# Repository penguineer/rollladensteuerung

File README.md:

Rolladensteuerung
=================

Content

controller:       Relais-Controller Rollläden
manuellsteuerung: Schalter für Manuellbetrieb Rollläden
raspberry:        Software für den Kontroll-Raspy
relaiskarte:      Relais Rollläden
switchboard:      Altes Schalterboard
tuer-controller:  I2C-Bridge zur Tür-Steuerung
tuer-steuerung:   Kontrolle Motor und Türstatus-Schalter
wd-switch:        Watchdog-Switch für Reset per Raspy

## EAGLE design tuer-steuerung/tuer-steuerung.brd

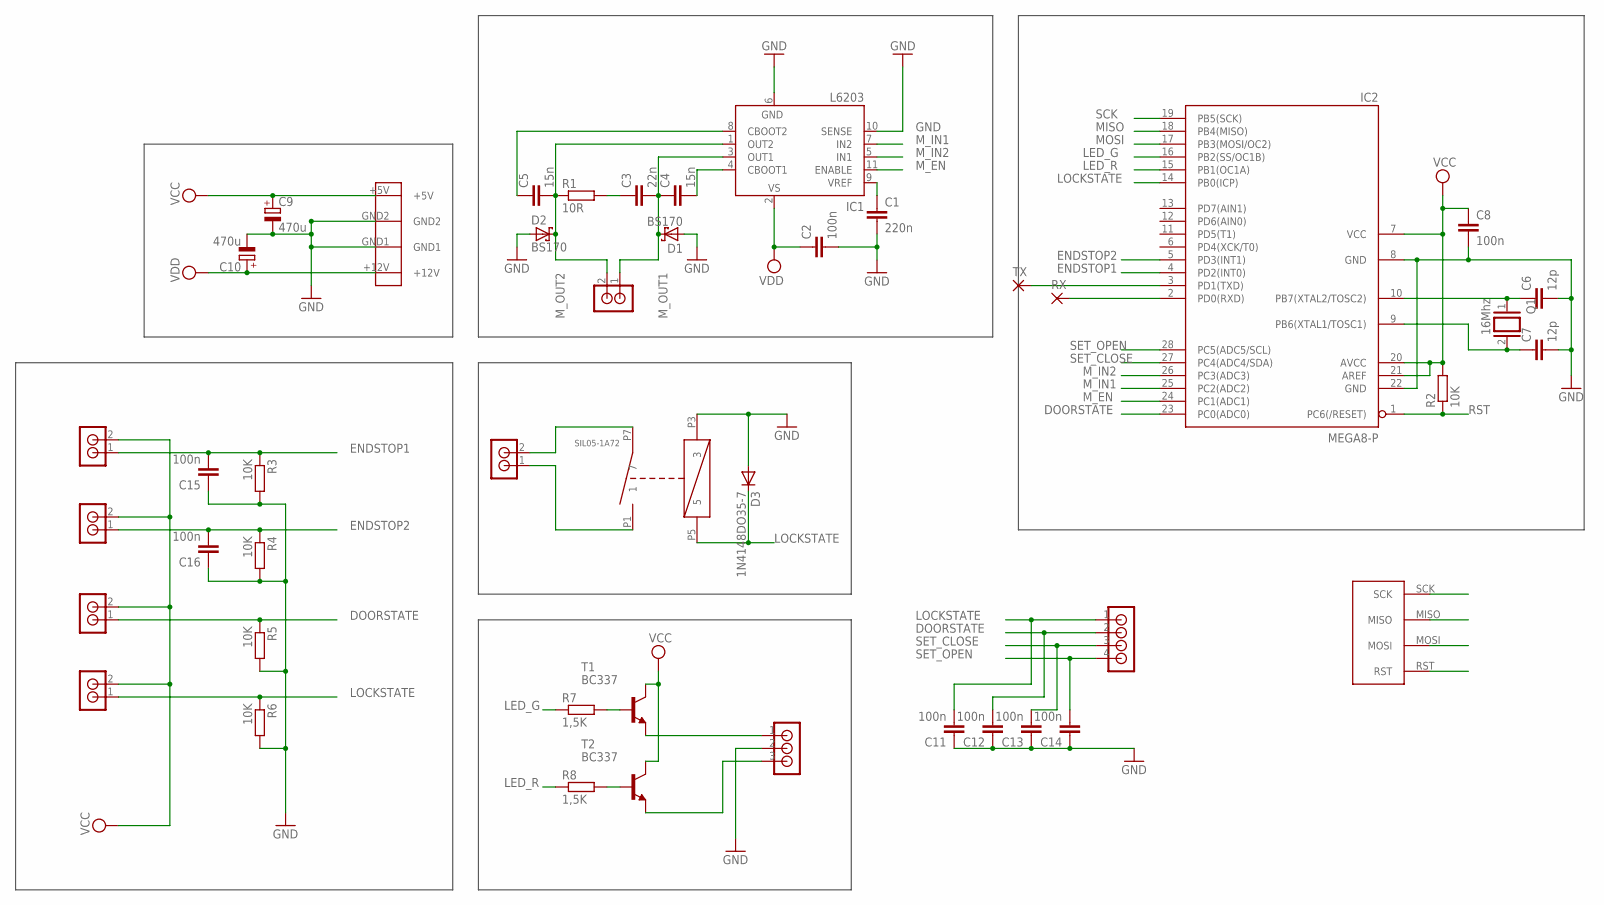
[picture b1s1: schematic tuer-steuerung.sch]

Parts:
C1: 220n; C025-024X044
C2, C8, C11, C12, C13, C14, C15, C16: 100n; C025-024X044
C3: 22n; C025-024X044
C4: 15n; C025-024X044
C5: 15n; C050-024X044
C6, C7: 12p; C050-025X075
C9, C10: 470u; TAP5-80
D1, D2: BS170; DO35-7
D3: 1N4148DO35-7; DO35-7
DOORSTATE: RIACON_101_2
ENDSTOP1, ENDSTOP2: RIACON_101_2
IC1: L6203; MULTIWATT-11
IC2: MEGA8-P; DIL28-3
LOCKSTATE: RIACON_101_2
MOTOR: RIACON_101_2
NERDSTERN: RIACON_101_2
Q1: 16Mhz; QS
R1: 10R; 0207/5V
R2, R3, R4, R5, R6: 10K; 0204/5
R7, R8: 1,5K; 0204/5
RX: 1,6/0,9
T1, T2: BC337; TO92
TX: 1,6/0,9
U$1: PSW_5
U$2: SIL05-1A72
U$3: AVR_ISP
U$4: RIACON_101_3
U$5: RIACON_101_4

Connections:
DOORSTATE: C12.2, DOORSTATE.1, IC2.23 (PC0(ADC0)), R5.1, U$5.2
ENDSTOP1: C15.2, ENDSTOP1.1, IC2.4 (PD2(INT0)), R3.1
ENDSTOP2: C16.2, ENDSTOP2.1, IC2.5 (PD3(INT1)), R4.1
GND: C1.2, C2.2, C6.2, C7.2, C8.2, C9.-, C10.-, C11.1, C12.1, C13.1, C14.1, C15.1, C16.1, D1.A, D2.A, D3.A, IC1.6 (GND), IC1.10 (SENSE), IC2.8 (GND), IC2.22 (GND), R3.2, R4.2, R5.2, R6.2, U$1.GND1, U$1.GND2, U$2.P3 (3), U$3.GND, U$4.2
LED_G: IC2.16 (PB2(SS/OC1B)), R7.1
LED_R: IC2.15 (PB1(OC1A)), R8.1
LOCKSTATE: C11.2, D3.C, IC2.14 (PB0(ICP)), LOCKSTATE.1, R6.1, U$2.P5 (5), U$5.1
MISO: IC2.18 (PB4(MISO)), U$3.MISO
MOSI: IC2.17 (PB3(MOSI/OC2)), U$3.MOSI
M_EN: IC1.11 (ENABLE), IC2.24 (PC1(ADC1))
M_IN1: IC1.7 (IN2), IC2.25 (PC2(ADC2))
M_IN2: IC1.5 (IN1), IC2.26 (PC3(ADC3))
M_OUT1: C3.2, C4.1, D1.C, IC1.3 (OUT1), MOTOR.1
M_OUT2: C5.2, D2.C, IC1.1 (OUT2), MOTOR.2, R1.1
unnamed: C6.1, IC2.10 (PB7(XTAL2/TOSC2)), Q1.1
unnamed: C7.1, IC2.9 (PB6(XTAL1/TOSC1)), Q1.2
unnamed: C1.1, IC1.9 (VREF)
unnamed: NERDSTERN.2, U$2.P7 (7)
unnamed: NERDSTERN.1, U$2.P1 (1)
unnamed: C3.1, R1.2
unnamed: C4.2, IC1.4 (CBOOT1)
unnamed: C5.1, IC1.8 (CBOOT2)
unnamed: R7.2, T1.2 (B)
unnamed: R8.2, T2.2 (B)
unnamed: T1.1 (E), U$4.1
unnamed: T2.1 (E), U$4.3
unnamed: IC2.3 (PD1(TXD)), TX.1
unnamed: IC2.2 (PD0(RXD)), RX.1
RST: IC2.1 (PC6(/RESET)), R2.1, U$3.RST
SCK: IC2.19 (PB5(SCK)), U$3.SCK
SET_CLOSE: C13.2, IC2.27 (PC4(ADC4/SDA)), U$5.3
SET_OPEN: C14.2, IC2.28 (PC5(ADC5/SCL)), U$5.4
VCC: C8.1, C9.+, DOORSTATE.2, ENDSTOP1.2, ENDSTOP2.2, IC2.7 (VCC), IC2.20 (AVCC), IC2.21 (AREF), LOCKSTATE.2, R2.2, T1.3 (C), T2.3 (C), U$1.+5V, U$3.VCC
VDD: C2.1, C10.+, IC1.2 (VS), U$1.+12V

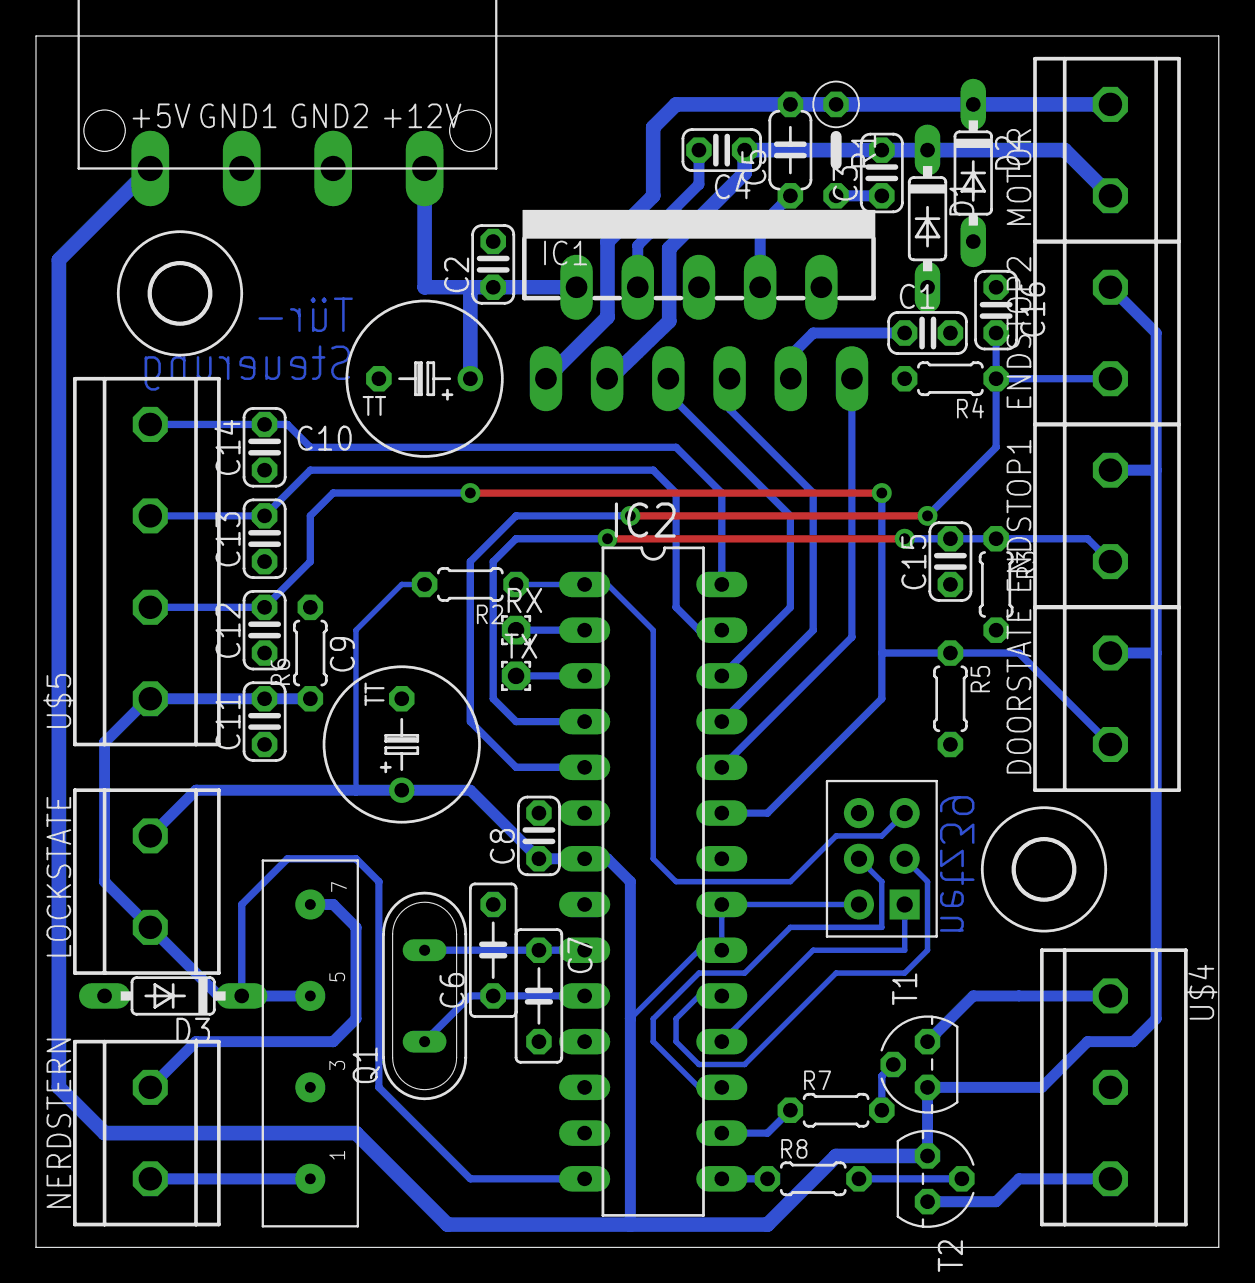
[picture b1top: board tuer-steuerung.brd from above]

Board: 2 copper layers, 65.7 x 67.3 mm, 47 parts (0 on the bottom side), 34 nets.

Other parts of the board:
U$6, U$7: 3,2

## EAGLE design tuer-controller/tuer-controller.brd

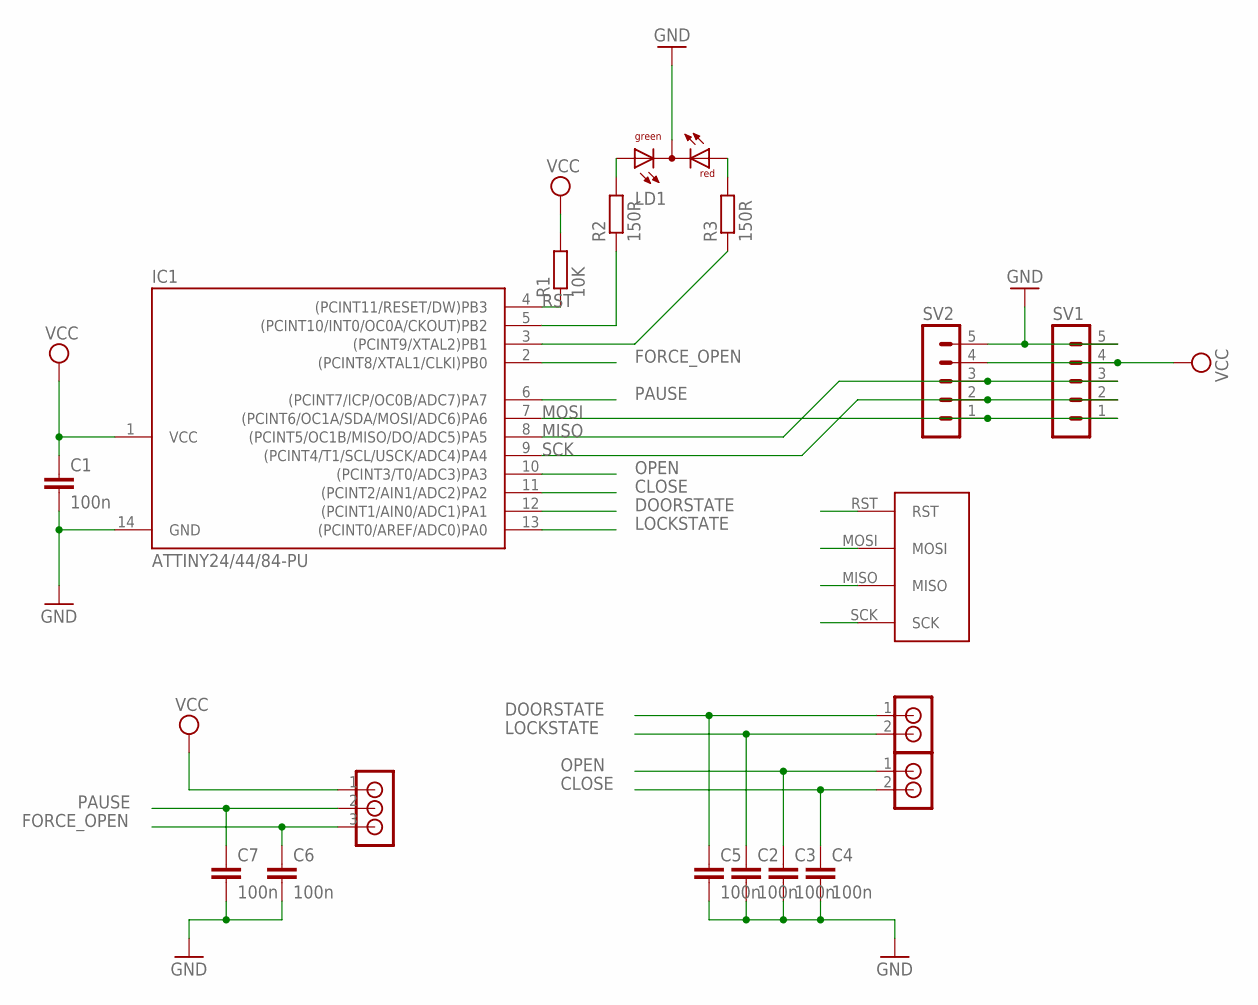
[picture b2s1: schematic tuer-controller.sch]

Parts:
C1, C2, C3, C4, C5, C6, C7: 100n; C025-024X044
IC1: ATTINY24/44/84-PU; DIL14
LD1: DUOLED-RG-C; DUOLED-C-5MM
R1: 10K; 0207/5V
R2: 150R; 0207/10
R3: 150R; 0207/15
SV1, SV2: MA05-1
U$1: AVR_ISP
U$2, U$3: RIACON_101_2
U$5: RIACON_59_3

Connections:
CLOSE: C4.1, IC1.11 ((PCINT2/AIN1/ADC2)PA2), U$3.2
DOORSTATE: C5.1, IC1.12 ((PCINT1/AIN0/ADC1)PA1), U$2.1
FORCE_OPEN: C6.1, IC1.2 ((PCINT8/XTAL1/CLKI)PB0), U$5.3
GND: C1.2, C2.2, C3.2, C4.2, C5.2, C6.2, C7.2, IC1.14 (GND), LD1.C, SV1.5, SV2.5, U$1.GND
LOCKSTATE: C2.1, IC1.13 ((PCINT0/AREF/ADC0)PA0), U$2.2
MISO: IC1.8 ((PCINT5/OC1B/MISO/DO/ADC5)PA5), SV1.3, SV2.3, U$1.MISO
MOSI: IC1.7 ((PCINT6/OC1A/SDA/MOSI/ADC6)PA6), SV1.1, SV2.1, U$1.MOSI
unnamed: IC1.5 ((PCINT10/INT0/OC0A/CKOUT)PB2), R2.1
unnamed: IC1.3 ((PCINT9/XTAL2)PB1), R3.1
unnamed: LD1.AX (AG), R2.2
unnamed: LD1.AR, R3.2
OPEN: C3.1, IC1.10 ((PCINT3/T0/ADC3)PA3), U$3.1
PAUSE: C7.1, IC1.6 ((PCINT7/ICP/OC0B/ADC7)PA7), U$5.2
RST: IC1.4 ((PCINT11/RESET/DW)PB3), R1.1, U$1.RST
SCK: IC1.9 ((PCINT4/T1/SCL/USCK/ADC4)PA4), SV1.2, SV2.2, U$1.SCK
VCC: C1.1, IC1.1 (VCC), R1.2, SV1.4, SV2.4, U$1.VCC, U$5.1

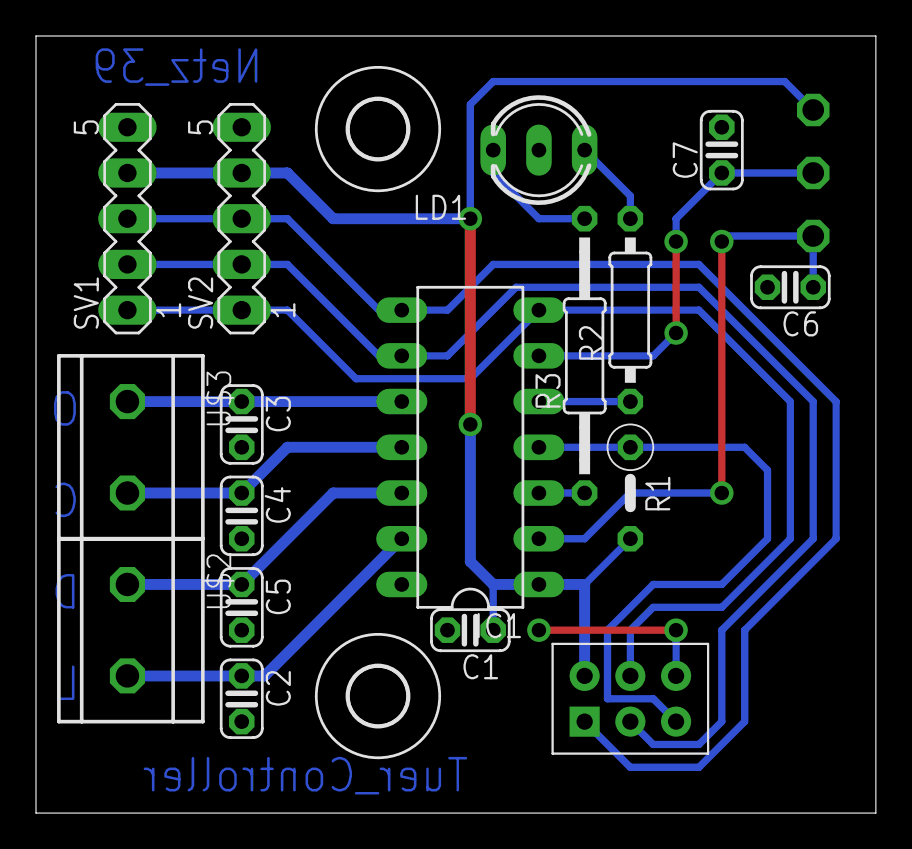
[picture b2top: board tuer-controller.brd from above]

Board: 2 copper layers, 46.7 x 43.2 mm, 20 parts (1 on the bottom side), 16 nets.

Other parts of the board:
U$4, U$6: 3,2

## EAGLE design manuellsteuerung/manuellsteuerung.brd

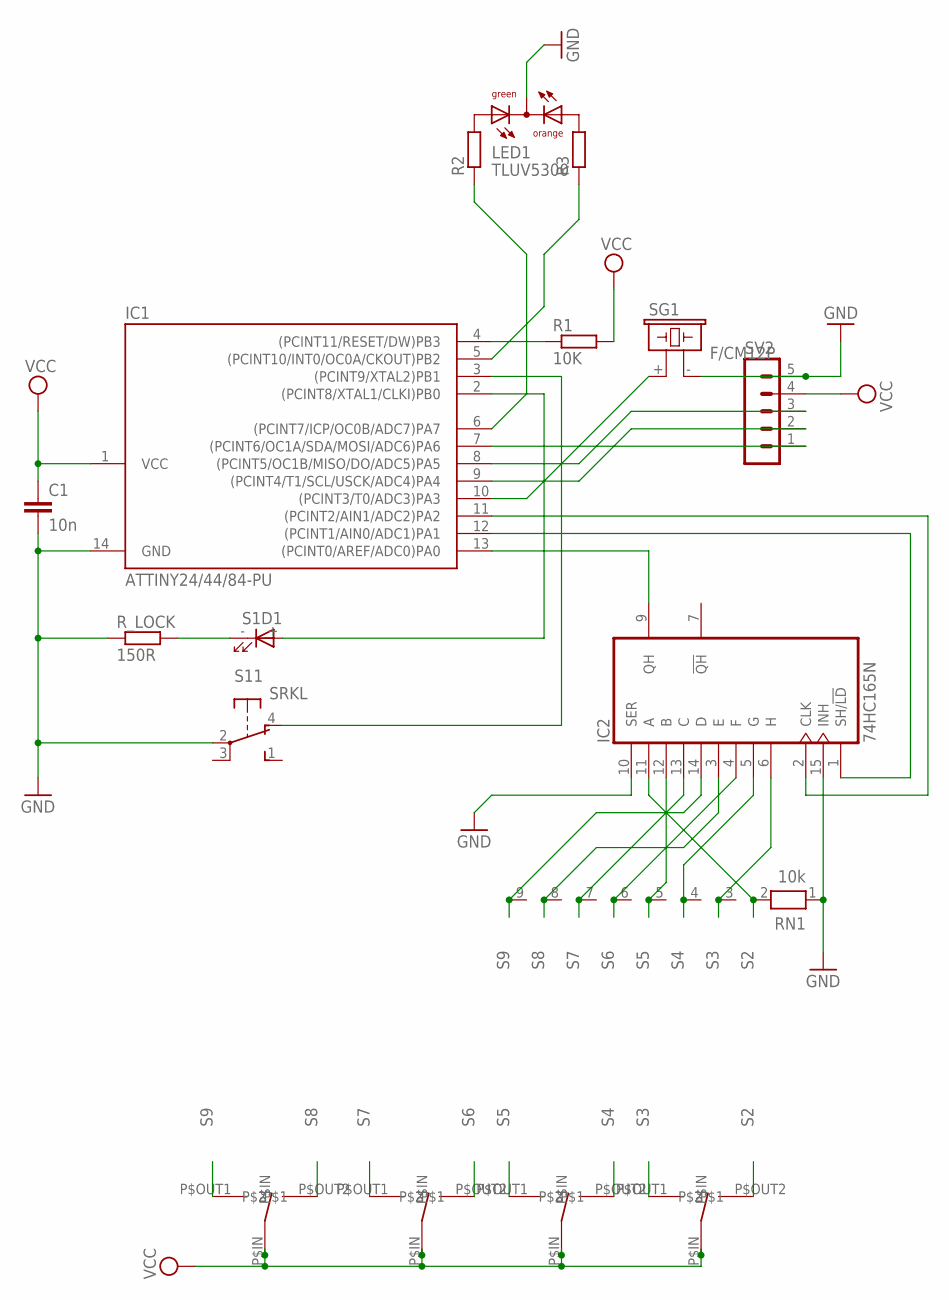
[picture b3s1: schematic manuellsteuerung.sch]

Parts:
C1: 10n; C025-024X044
IC1: ATTINY24/44/84-PU; DIL14
IC2: 74HC165N; DIL16
LED1: TLUV5300
R1: 10K; 0207/7
R2, R3: R-EU_0207/7; 0207/7
RN1: 10k; RN-9
R_LOCK: 150R; 0207/10
S1: SRKL
SG1: F/CM12P
SV2: MA05-1
U$1, U$2, U$3, U$4: MS_500E

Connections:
GND: C1.2, IC1.14 (GND), IC2.8 (GND), IC2.10 (SER), IC2.15 (INH), LED1.CC, RN1.1, R_LOCK.1, S1.2, SG1.- (2), SV2.5
MISO: IC1.8 ((PCINT5/OC1B/MISO/DO/ADC5)PA5), SV2.3
MOSI: IC1.7 ((PCINT6/OC1A/SDA/MOSI/ADC6)PA6), SV2.1
unnamed: IC1.13 ((PCINT0/AREF/ADC0)PA0), IC2.9 (QH)
unnamed: IC1.12 ((PCINT1/AIN0/ADC1)PA1), IC2.1 (SH/!LD)
unnamed: IC1.11 ((PCINT2/AIN1/ADC2)PA2), IC2.2 (CLK)
unnamed: R_LOCK.2, S1.- (C)
unnamed: IC1.2 ((PCINT8/XTAL1/CLKI)PB0), S1.+ (A)
unnamed: IC1.3 ((PCINT9/XTAL2)PB1), S1.4 (O)
unnamed: IC1.10 ((PCINT3/T0/ADC3)PA3), SG1.+ (1)
unnamed: LED1.AG, R2.2
unnamed: LED1.AO, R3.2
unnamed: IC1.6 ((PCINT7/ICP/OC0B/ADC7)PA7), R2.1
unnamed: IC1.5 ((PCINT10/INT0/OC0A/CKOUT)PB2), R3.1
RESET: IC1.4 ((PCINT11/RESET/DW)PB3), R1.1
S2: IC2.11 (A), RN1.2, U$4.P$OUT2
S3: IC2.6 (H), RN1.3, U$4.P$OUT1
S4: IC2.5 (G), RN1.4, U$1.P$OUT2
S5: IC2.12 (B), RN1.5, U$1.P$OUT1
S6: IC2.4 (F), RN1.6, U$3.P$OUT2
S7: IC2.13 (C), RN1.7, U$3.P$OUT1
S8: IC2.3 (E), RN1.8, U$2.P$OUT2
S9: IC2.14 (D), RN1.9, U$2.P$OUT1
SCK: IC1.9 ((PCINT4/T1/SCL/USCK/ADC4)PA4), SV2.2
VCC: C1.1, IC1.1 (VCC), IC2.16 (VCC), R1.2, SV2.4, U$1.P$IN, U$2.P$IN, U$3.P$IN, U$4.P$IN

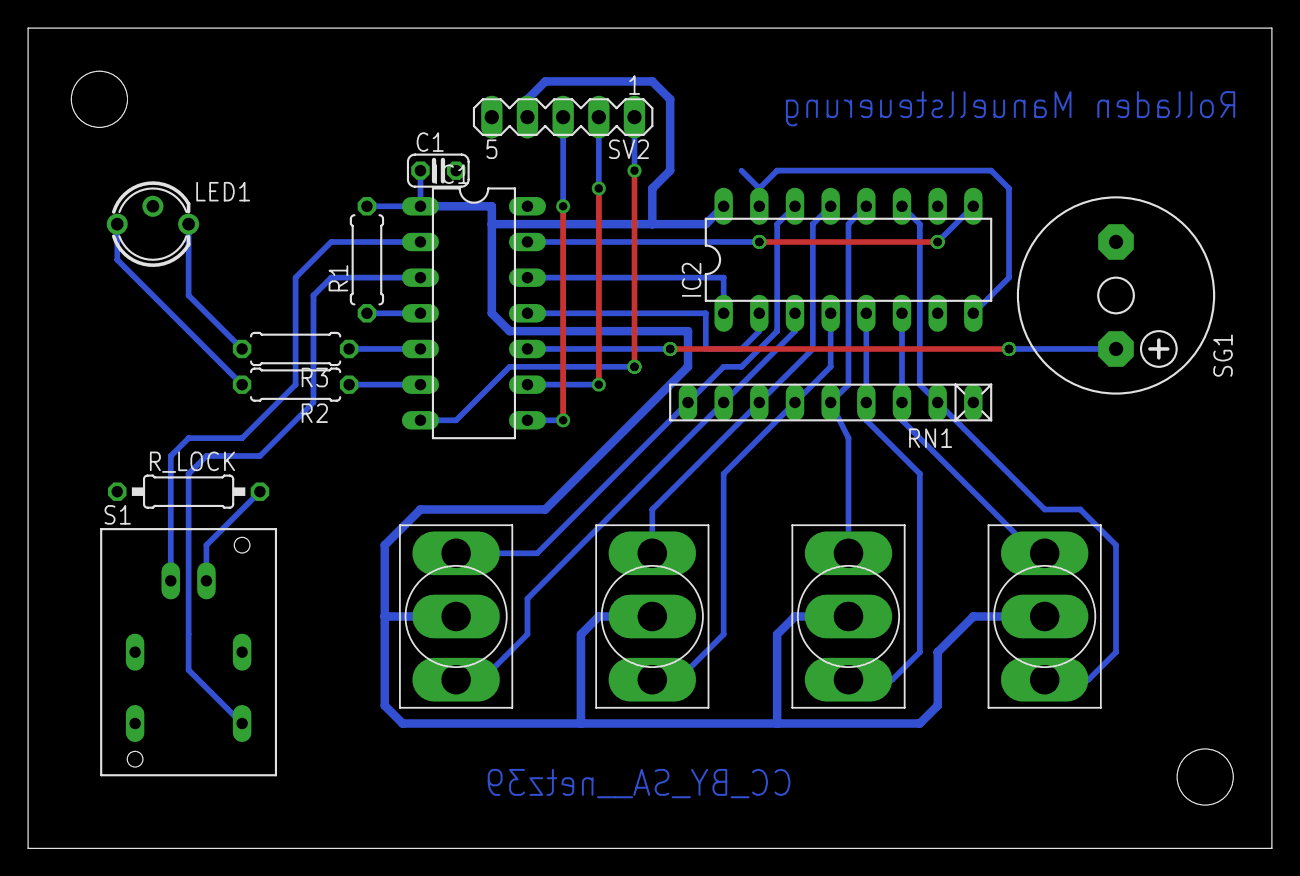
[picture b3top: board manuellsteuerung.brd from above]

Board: 2 copper layers, 88.6 x 58.4 mm, 16 parts (0 on the bottom side), 25 nets.

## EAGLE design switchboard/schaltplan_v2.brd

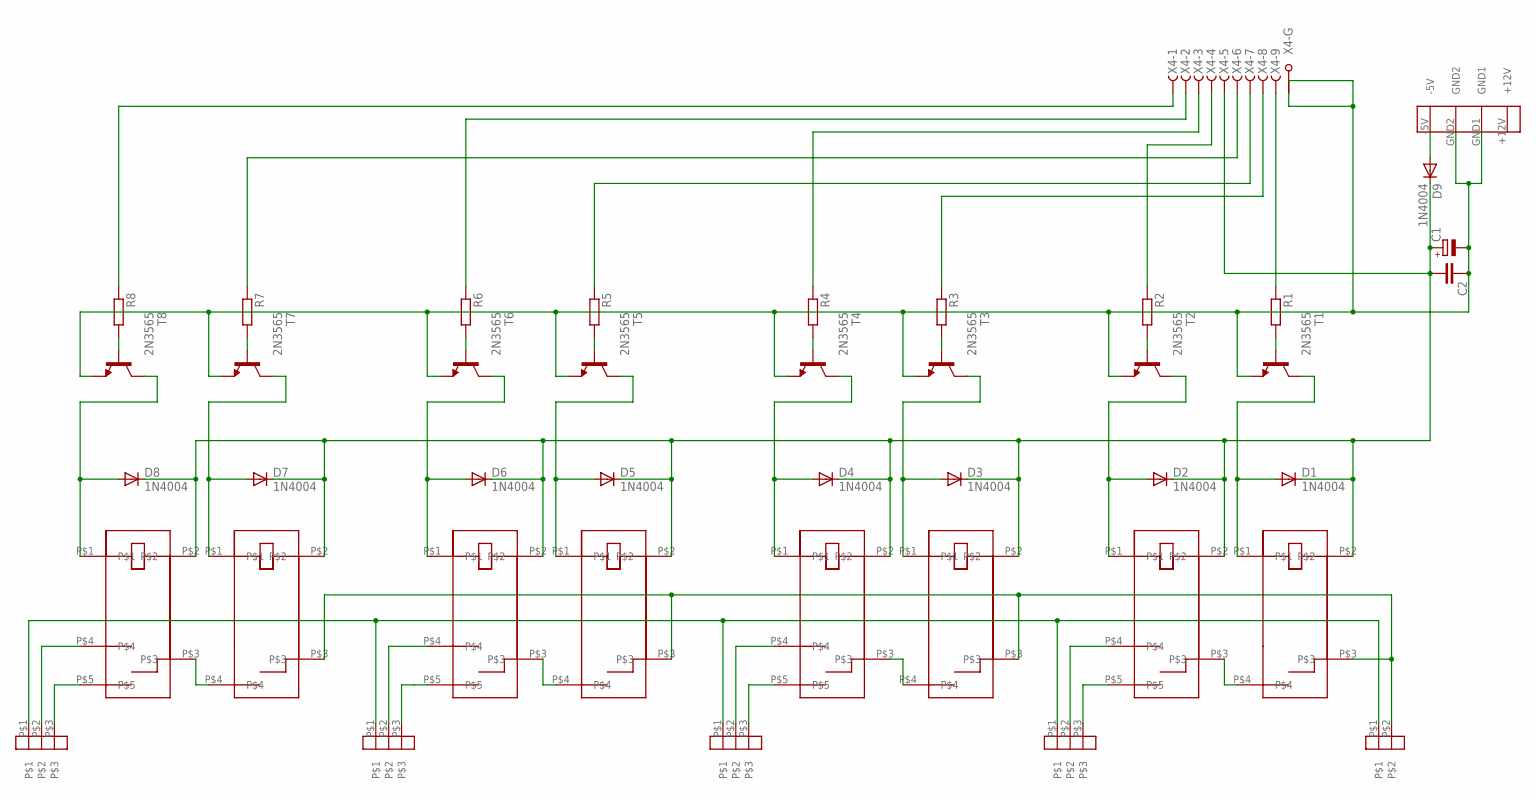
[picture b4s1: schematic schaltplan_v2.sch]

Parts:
C1: CPOL-EUE3.5-8; E3,5-8
C2: C-EU025-030X050; C025-030X050
D1, D2, D3, D4, D5, D6, D7, D8, D9: 1N4004; DO41-10
R1, R2, R3, R4, R5, R6, R7, R8: R-EU_0207/7; 0207/7
T1, T2, T3, T4, T5, T6, T7, T8: 2N3565; TO92
U$1, U$3, U$5, U$7: JS_05_MN_KT
U$2, U$4, U$6, U$8: JS_05_N_K
U$9: WAGO_734_262
U$10, U$11, U$12, U$13: WAGO_734_263
U$14: PSW_5
X4: F09HPS; F09HP

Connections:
GND: C1.-, C2.1, T1.3 (E), T2.3 (E), T3.3 (E), T4.3 (E), T5.3 (E), T6.3 (E), T7.3 (E), T8.3 (E), U$14.GND1, U$14.GND2, X4.G1, X4.G2
GND2: U$9.P$1, U$10.P$1, U$11.P$1, U$12.P$1, U$13.P$1
unnamed: U$2.P$5, U$10.P$3
unnamed: U$2.P$4, U$10.P$2
unnamed: U$1.P$4, U$2.P$3
unnamed: U$1.P$3, U$3.P$3, U$5.P$3, U$7.P$3, U$9.P$2
unnamed: D1.A, T1.1 (C), U$1.P$1
unnamed: D9.A, U$14.-5V
unnamed: R1.2, T1.2 (B)
unnamed: D2.A, T2.1 (C), U$2.P$1
unnamed: R5.1, X4.7 (F)
unnamed: D3.A, T3.1 (C), U$3.P$1
unnamed: R6.2, T6.2 (B)
unnamed: R6.1, X4.2 (F)
unnamed: R8.1, X4.1 (F)
unnamed: U$4.P$5, U$11.P$3
unnamed: U$4.P$4, U$11.P$2
unnamed: U$3.P$4, U$4.P$3
unnamed: D4.A, T4.1 (C), U$4.P$1
unnamed: R7.1, X4.6 (F)
unnamed: R3.2, T3.2 (B)
unnamed: R4.1, X4.3 (F)
unnamed: D5.A, T5.1 (C), U$5.P$1
unnamed: R2.1, X4.4 (F)
unnamed: R2.2, T2.2 (B)
unnamed: R4.2, T4.2 (B)
unnamed: U$6.P$5, U$12.P$3
unnamed: U$6.P$4, U$12.P$2
unnamed: U$5.P$4, U$6.P$3
unnamed: D6.A, T6.1 (C), U$6.P$1
unnamed: D7.A, T7.1 (C), U$7.P$1
unnamed: D8.A, T8.1 (C), U$8.P$1
unnamed: R5.2, T5.2 (B)
unnamed: R3.1, X4.8 (F)
unnamed: R1.1, X4.9 (F)
unnamed: R8.2, T8.2 (B)
unnamed: U$8.P$5, U$13.P$3
unnamed: U$8.P$4, U$13.P$2
unnamed: U$7.P$4, U$8.P$3
unnamed: R7.2, T7.2 (B)
V+: C1.+, C2.2, D1.C, D2.C, D3.C, D4.C, D5.C, D6.C, D7.C, D8.C, D9.C, U$1.P$2, U$2.P$2, U$3.P$2, U$4.P$2, U$5.P$2, U$6.P$2, U$7.P$2, U$8.P$2, X4.5 (F)

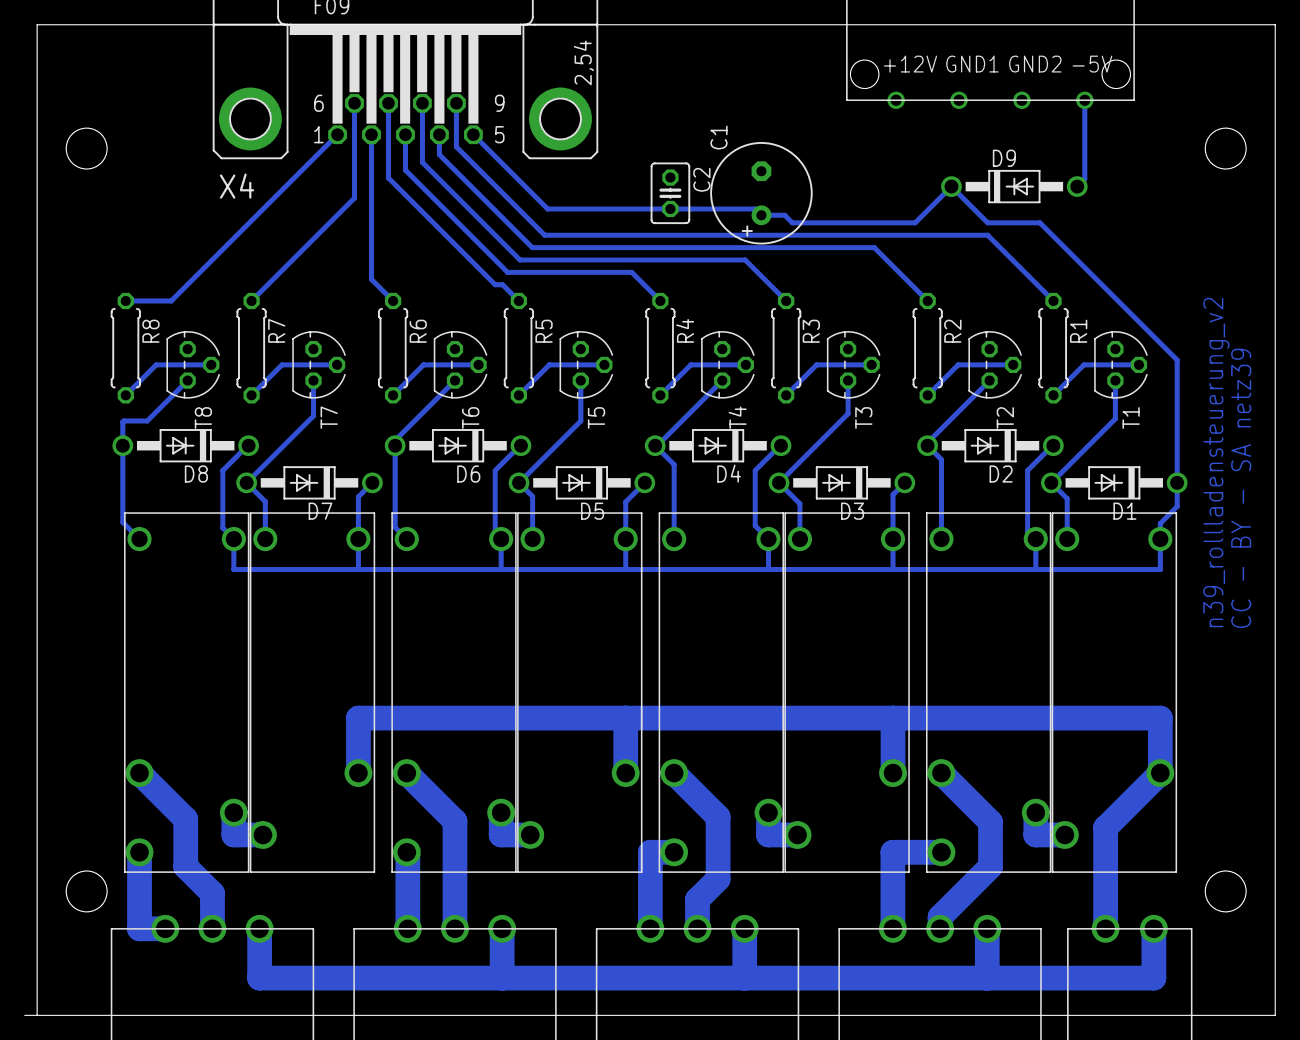
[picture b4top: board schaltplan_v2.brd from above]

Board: 2 copper layers, 101.0 x 80.0 mm, 42 parts (0 on the bottom side), 41 nets.

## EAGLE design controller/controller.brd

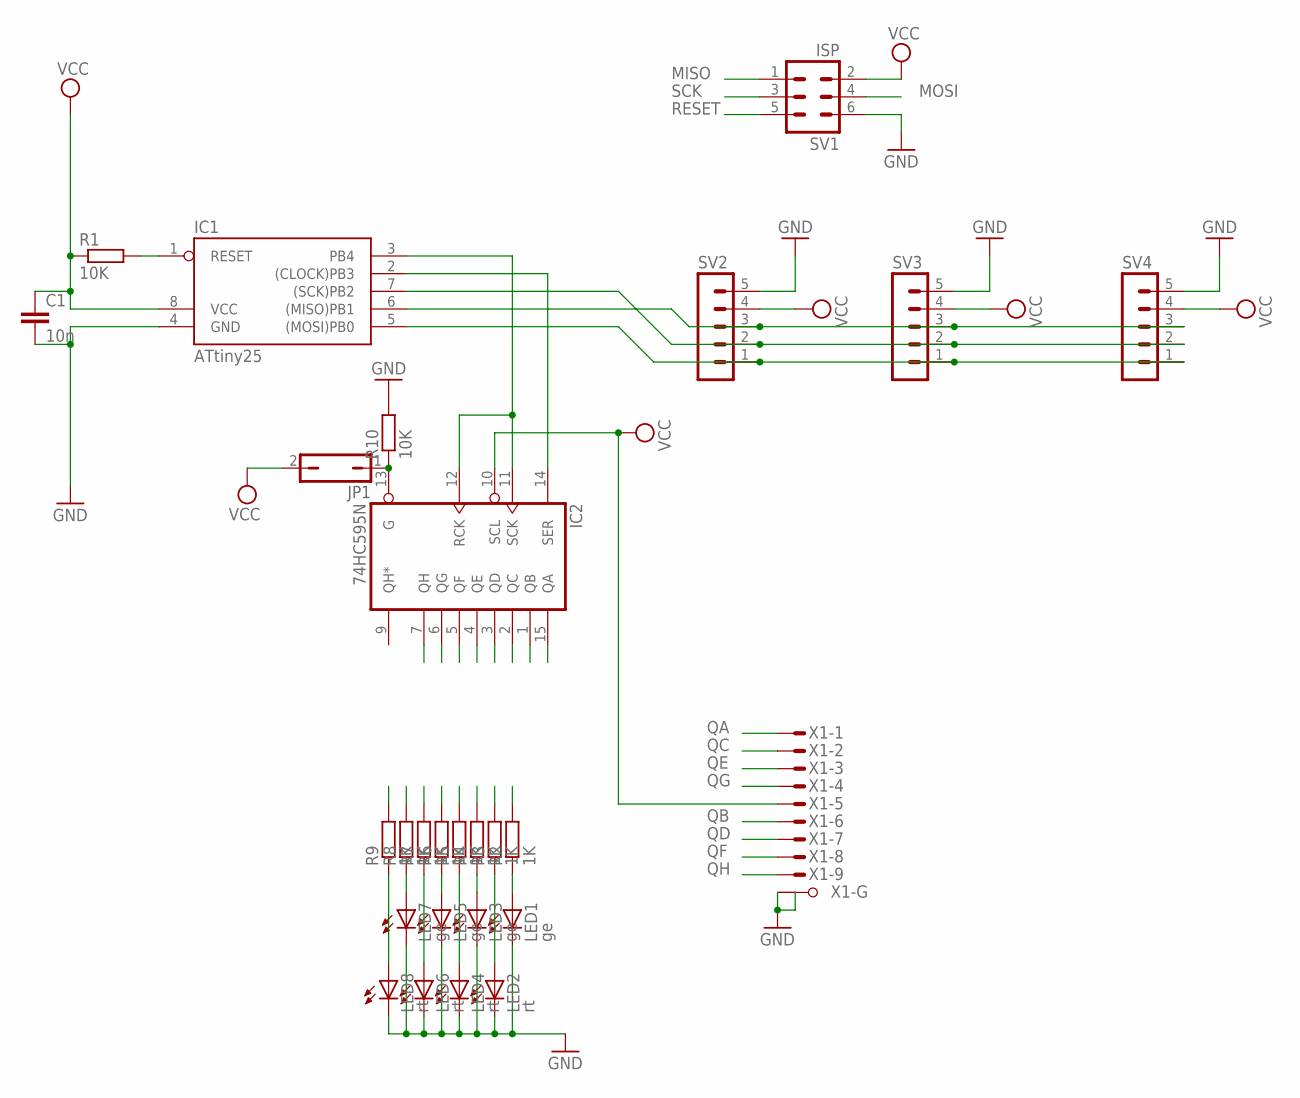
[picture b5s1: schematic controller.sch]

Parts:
C1: 10n; C025-024X044
IC1: ATtiny25; DIL08
IC2: 74HC595N; DIL16
JP1: JP1Q; JP1
LED1, LED3, LED5, LED7: ge; LED5MM
LED2, LED4, LED6, LED8: rt; LED5MM
R1, R10: 10K; 0207/7
R2, R3, R4, R5, R6, R7, R8, R9: 1K; 0309/12
SV1: ISP; MA03-2
SV2, SV3, SV4: MA05-1
X1: M09HPS; M09HP

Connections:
GND: C1.2, IC1.4 (GND), IC2.8 (GND), LED1.K (C), LED2.K (C), LED3.K (C), LED4.K (C), LED5.K (C), LED6.K (C), LED7.K (C), LED8.K (C), R10.2, SV1.6, SV2.5, SV3.5, SV4.5, X1.G1, X1.G2
MISO: IC1.6 ((MISO)PB1), SV1.1, SV2.3, SV3.3, SV4.3
MOSI: IC1.5 ((MOSI)PB0), SV1.4, SV2.1, SV3.1, SV4.1
unnamed: IC1.2 ((CLOCK)PB3), IC2.14 (SER)
unnamed: IC1.3 (PB4), IC2.11 (SCK), IC2.12 (RCK)
unnamed: LED1.A, R2.1
unnamed: LED2.A, R3.1
unnamed: LED3.A, R4.1
unnamed: LED4.A, R5.1
unnamed: LED5.A, R6.1
unnamed: LED6.A, R7.1
unnamed: LED7.A, R8.1
unnamed: LED8.A, R9.1
QA: IC2.15 (QA), R2.2, X1.1 (M)
QB: IC2.1 (QB), R6.2, X1.6 (M)
QC: IC2.2 (QC), R3.2, X1.2 (M)
QD: IC2.3 (QD), R7.2, X1.7 (M)
QE: IC2.4 (QE), R4.2, X1.3 (M)
QF: IC2.5 (QF), R8.2, X1.8 (M)
QG: IC2.6 (QG), R5.2, X1.4 (M)
QH: IC2.7 (QH), R9.2, X1.9 (M)
REG_DISABLE: IC2.13 (G), JP1.1, R10.1
RESET: IC1.1 (RESET), R1.2, SV1.5
SCK: IC1.7 ((SCK)PB2), SV1.3, SV2.2, SV3.2, SV4.2
VCC: C1.1, IC1.8 (VCC), IC2.10 (SCL), IC2.16 (VCC), JP1.2, R1.1, SV1.2, SV2.4, SV3.4, SV4.4, X1.5 (M)

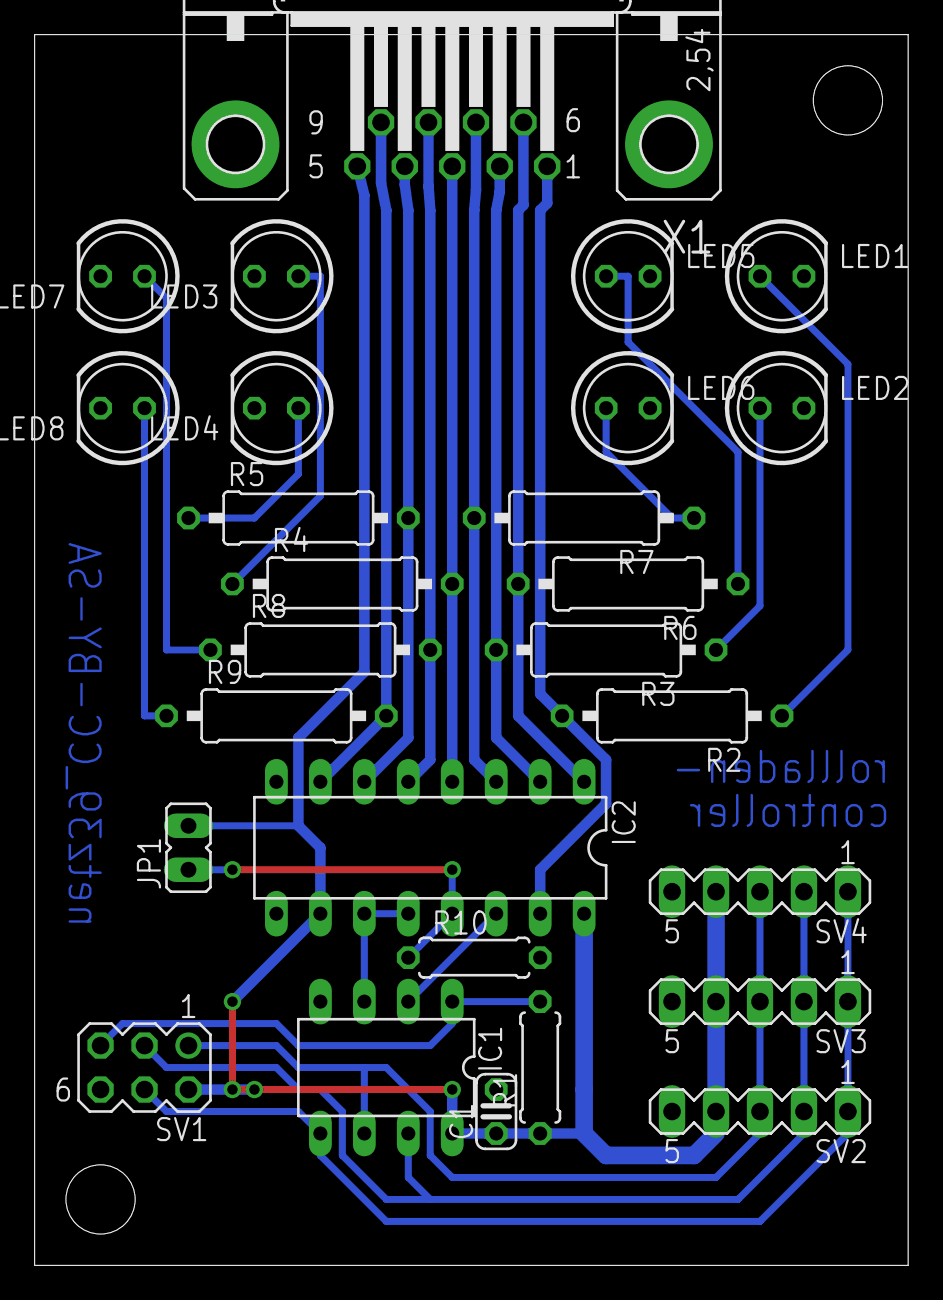
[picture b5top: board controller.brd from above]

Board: 2 copper layers, 50.5 x 71.1 mm, 27 parts (0 on the bottom side), 25 nets.

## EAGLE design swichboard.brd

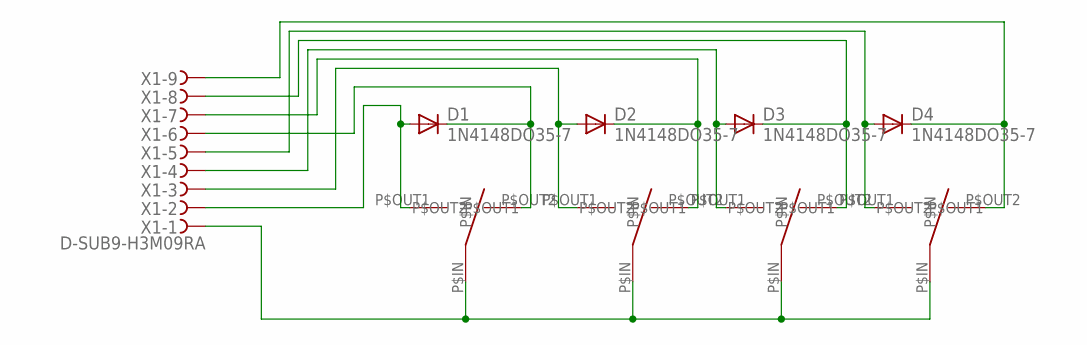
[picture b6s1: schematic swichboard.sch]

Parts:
D1, D2, D3, D4: 1N4148DO35-7; DO35-7
U$1, U$2, U$3, U$4: MS500E
X1: D-SUB9-H3M09RA; H3M09RA

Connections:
unnamed: D1.A, U$1.P$OUT1, X1.2
unnamed: D1.C, U$1.P$OUT2, X1.6
unnamed: D2.A, U$2.P$OUT1, X1.3
unnamed: D2.C, U$2.P$OUT2, X1.7
unnamed: D3.A, U$3.P$OUT1, X1.4
unnamed: D3.C, U$3.P$OUT2, X1.8
unnamed: D4.A, U$4.P$OUT1, X1.5
unnamed: D4.C, U$4.P$OUT2, X1.9
VCC: U$1.P$IN, U$2.P$IN, U$3.P$IN, U$4.P$IN, X1.1

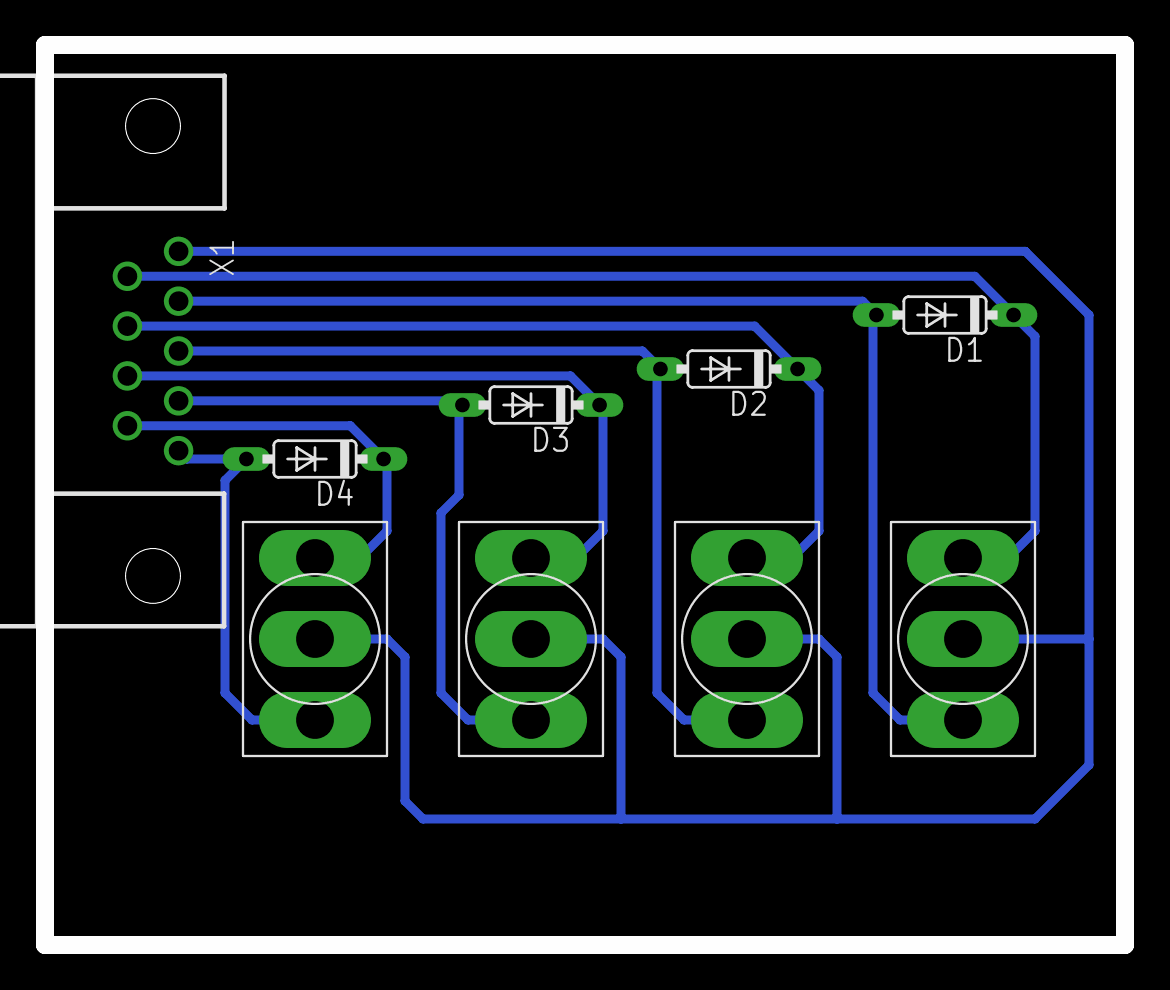
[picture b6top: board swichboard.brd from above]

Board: 2 copper layers, 60.0 x 50.0 mm, 9 parts (0 on the bottom side), 9 nets.

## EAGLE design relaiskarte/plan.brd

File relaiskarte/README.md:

netz39_rollladensteuerung
=========================

schaltplaene etc.

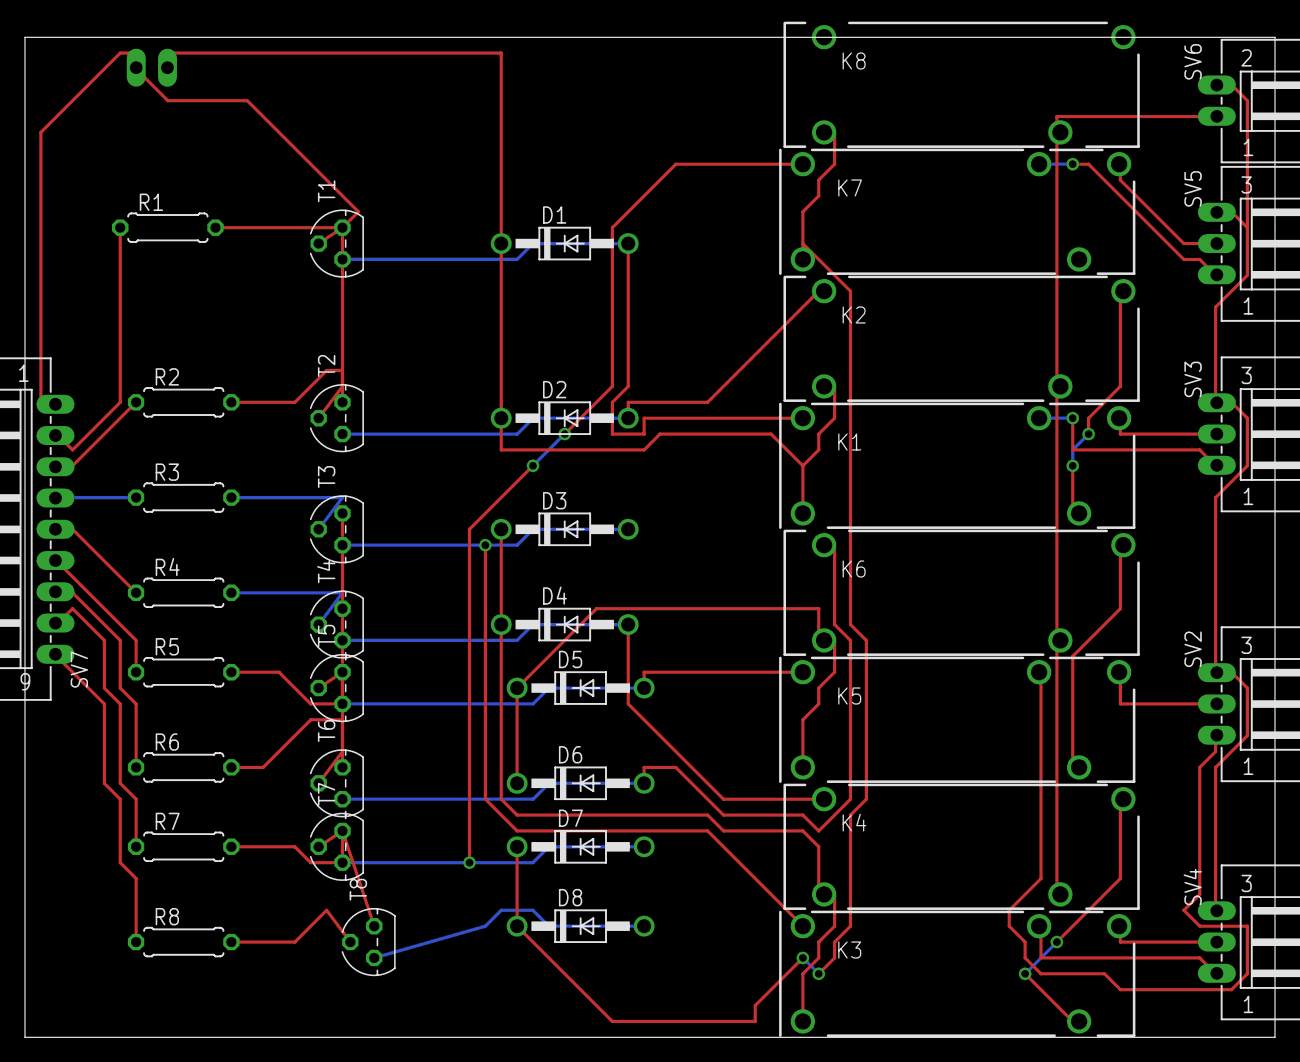
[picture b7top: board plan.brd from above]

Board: 2 copper layers, 100.0 x 80.0 mm, 39 parts (1 on the bottom side), 45 nets.

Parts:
D1, D2, D3, D4, D5, D6, D7, D8: 1N4004; DO41-10
K1, K3, K5, K7: RY210005; RY-II
K2, K4, K6, K8: RY230005; RY-II1
R1, R2, R3, R4, R5, R6, R7, R8: 0207/7
SV1, SV6: L02P
SV2, SV3, SV4, SV5: L03P
SV7: L09P
T1, T2, T3, T4, T5, T6, T7, T8: TO92

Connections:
unnamed: R1.2, T1.2
unnamed: R2.2, T2.2
unnamed: SV1.1, SV7.1, T1.1, T2.1
unnamed: R3.2, T3.2
unnamed: D1.A, K1.A2, T1.3
unnamed: D2.A, K2.A2, T2.3
unnamed: D1.C, D2.C, K1.A1, K2.A1, SV1.2
unnamed: R4.2, T4.2
unnamed: K1.11, K2.14
unnamed: SV2.3, SV3.3, SV4.3, SV5.3, SV6.2
unnamed: D3.A, K3.A2, T3.3
unnamed: D4.A, K4.A2, T4.3
unnamed: D3.C, D4.C, K3.A1, K4.A1
unnamed: K3.11, K4.14
unnamed: K3.14, SV4.2
unnamed: K3.12, SV4.1
unnamed: K1.14, SV3.2
unnamed: K1.12, SV3.1
unnamed: K2.11, K4.11, K6.11, K8.11, SV6.1
unnamed: R1.1, SV7.2
unnamed: R5.2, T5.2
unnamed: R6.2, T6.2
unnamed: T3.1, T4.1, T5.1, T6.1
unnamed: D5.A, K5.A2, T5.3
unnamed: D6.A, K6.A2, T6.3
unnamed: D5.C, D6.C, K5.A1, K6.A1
unnamed: K5.11, K6.14
unnamed: R7.2, T7.2
unnamed: R8.2, T8.2
unnamed: T7.1, T8.1
unnamed: D7.A, K7.A2, T7.3
unnamed: D8.A, K8.A2, T8.3
unnamed: D7.C, D8.C, K7.A1, K8.A1
unnamed: K7.11, K8.14
unnamed: K7.14, SV5.2
unnamed: K7.12, SV5.1
unnamed: K5.14, SV2.2
unnamed: K5.12, SV2.1
unnamed: R8.1, SV7.9
unnamed: R6.1, SV7.7
unnamed: R5.1, SV7.6
unnamed: R4.1, SV7.5
unnamed: R3.1, SV7.4
unnamed: R2.1, SV7.3
unnamed: R7.1, SV7.8
